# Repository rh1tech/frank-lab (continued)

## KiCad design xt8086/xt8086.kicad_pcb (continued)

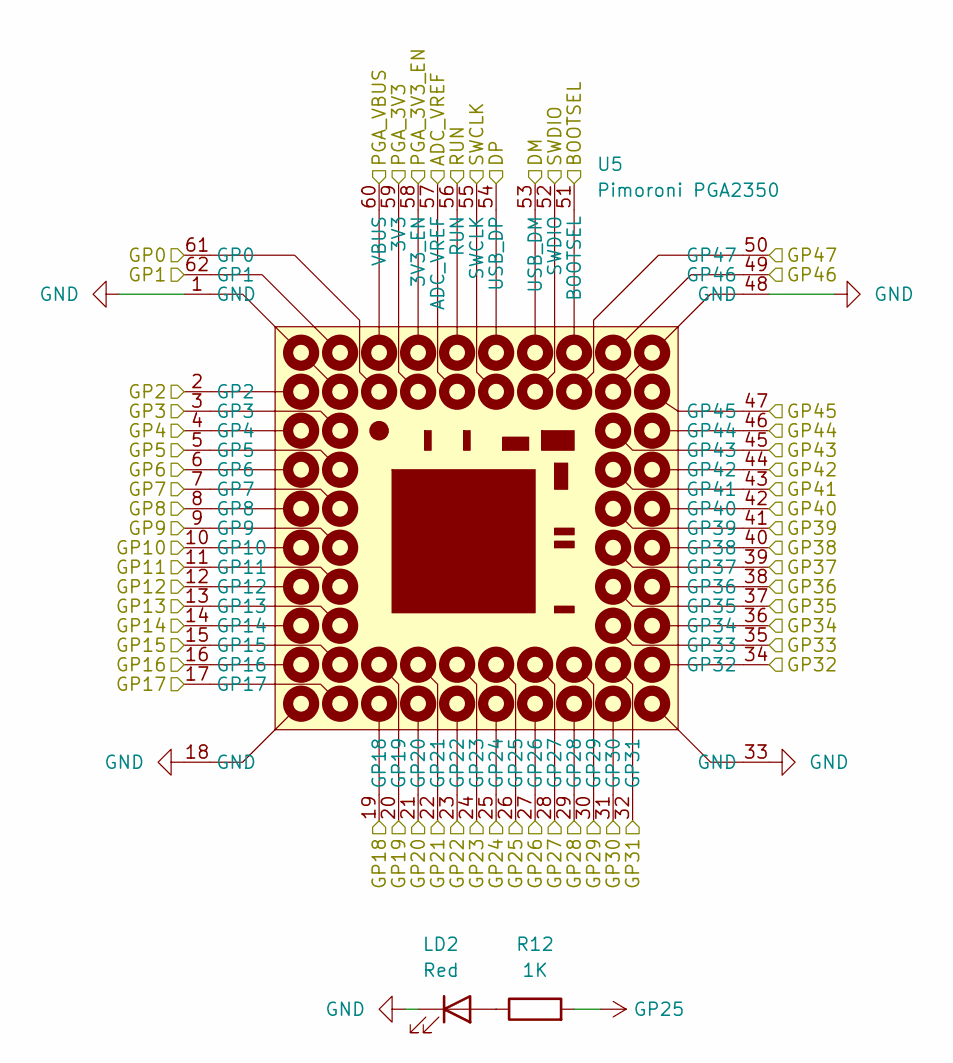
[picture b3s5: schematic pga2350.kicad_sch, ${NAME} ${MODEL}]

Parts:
LD2: Red; LED_0805_2012Metric_Pad1.15x1.40mm_HandSolder
R12: 1K; R_0805_2012Metric
U5: Pimoroni PGA2350; PGA2350

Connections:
+3V3: U5.59 (3V3); also elsewhere on the board
/A16/GP16: U5.16 (GP16); also elsewhere on the board
/A17/GP17: U5.17 (GP17); also elsewhere on the board
/A18/GP18: U5.19 (GP18); also elsewhere on the board
/A19/GP19: U5.20 (GP19); also elsewhere on the board
/AD0/GP0: U5.61 (GP0); also elsewhere on the board
/AD1/GP1: U5.62 (GP1); also elsewhere on the board
/AD2/GP2: U5.2 (GP2); also elsewhere on the board
/AD3/GP3: U5.3 (GP3); also elsewhere on the board
/AD4/GP4: U5.4 (GP4); also elsewhere on the board
/AD5/GP5: U5.5 (GP5); also elsewhere on the board
/AD6/GP6: U5.6 (GP6); also elsewhere on the board
/AD7/GP7: U5.7 (GP7); also elsewhere on the board
/AD8/GP8: U5.8 (GP8); also elsewhere on the board
/AD9/GP9: U5.9 (GP9); also elsewhere on the board
/AD10/GP10: U5.10 (GP10); also elsewhere on the board
/AD11/GP11: U5.11 (GP11); also elsewhere on the board
/AD12/GP12: U5.12 (GP12); also elsewhere on the board
/AD13/GP13: U5.13 (GP13); also elsewhere on the board
/AD14/GP14: U5.14 (GP14); also elsewhere on the board
/AD15/GP15: U5.15 (GP15); also elsewhere on the board
/ALE/GP20: U5.21 (GP20); also elsewhere on the board
/Audio/SPEAKER: U5.49 (GP46); also elsewhere on the board
/BOOTSEL: U5.51 (BOOTSEL); also elsewhere on the board
/CLK/GP29: U5.30 (GP29); also elsewhere on the board
/GP27: U5.28 (GP27); also elsewhere on the board
/INTA/GP23: U5.24 (GP23); also elsewhere on the board
/INTR/GP26: U5.27 (GP26); also elsewhere on the board
/MIO/GP24: U5.25 (GP24); also elsewhere on the board
/Micro SD/CDDAT3: U5.43 (GP41); also elsewhere on the board
/Micro SD/CLK: U5.44 (GP42); also elsewhere on the board
/Micro SD/CMD: U5.45 (GP43); also elsewhere on the board
/Micro SD/DAT0: U5.42 (GP40); also elsewhere on the board
/PGA2350/ADC_VREF: U5.57 (ADC_VREF)
/PGA2350/DM: U5.53 (USB_DM); also elsewhere on the board
/PGA2350/DP: U5.54 (USB_DP); also elsewhere on the board
/PGA2350/GP30: U5.31 (GP30); also elsewhere on the board
/PGA2350/GP31: U5.32 (GP31); also elsewhere on the board
/PGA2350/GP32: U5.34 (GP32); also elsewhere on the board
/PGA2350/GP33: U5.35 (GP33); also elsewhere on the board
/PGA2350/GP34: U5.36 (GP34); also elsewhere on the board
/PGA2350/GP35: U5.37 (GP35); also elsewhere on the board
/PGA2350/GP36: U5.38 (GP36); also elsewhere on the board
/PGA2350/GP37: U5.39 (GP37); also elsewhere on the board
/PGA2350/GP38: U5.40 (GP38)
/PGA2350/GP39: U5.41 (GP39)
/PGA2350/GP47: U5.50 (GP47)
/PGA2350/PGA_3V3_EN: U5.58 (3V3_EN)
/RD/GP21: U5.22 (GP21); also elsewhere on the board
/RESET/GP28: U5.29 (GP28); also elsewhere on the board
/RUN: U5.56 (RUN); also elsewhere on the board
/SWCLK: U5.55 (SWCLK); also elsewhere on the board
/SWDIO: U5.52 (SWDIO); also elsewhere on the board
/UART0_RX: U5.47 (GP45); also elsewhere on the board
/UART0_TX: U5.46 (GP44); also elsewhere on the board
/WR/GP22: U5.23 (GP22); also elsewhere on the board
GND: LD2.1 (K), U5.1 (GND), U5.18 (GND), U5.33 (GND), U5.48 (GND); also elsewhere on the board
GP25: R12.2, U5.26 (GP25); also elsewhere on the board
unnamed: LD2.2 (A), R12.1
VBUS: U5.60 (VBUS); also elsewhere on the board

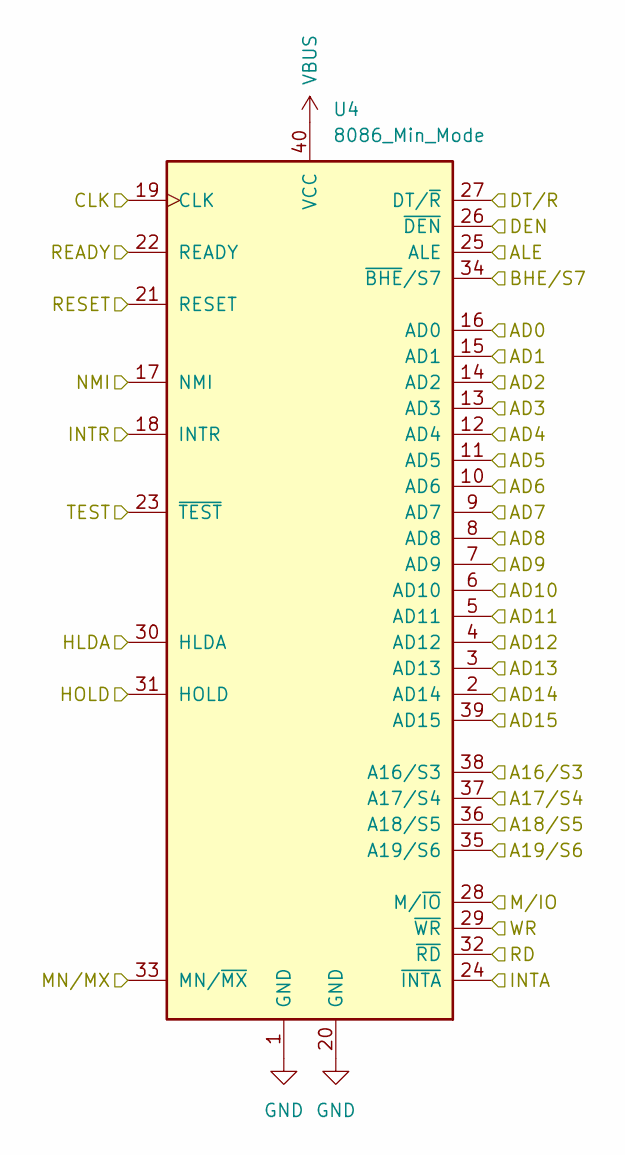
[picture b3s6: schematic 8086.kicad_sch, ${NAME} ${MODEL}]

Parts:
U4: 8086_Min_Mode; DIP-40_W15.24mm

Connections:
/A16/GP16: U4.38 (A16/S3); also elsewhere on the board
/A17/GP17: U4.37 (A17/S4); also elsewhere on the board
/A18/GP18: U4.36 (A18/S5); also elsewhere on the board
/A19/GP19: U4.35 (A19/S6); also elsewhere on the board
/AD0/GP0: U4.16 (AD0); also elsewhere on the board
/AD1/GP1: U4.15 (AD1); also elsewhere on the board
/AD2/GP2: U4.14 (AD2); also elsewhere on the board
/AD3/GP3: U4.13 (AD3); also elsewhere on the board
/AD4/GP4: U4.12 (AD4); also elsewhere on the board
/AD5/GP5: U4.11 (AD5); also elsewhere on the board
/AD6/GP6: U4.10 (AD6); also elsewhere on the board
/AD7/GP7: U4.9 (AD7); also elsewhere on the board
/AD8/GP8: U4.8 (AD8); also elsewhere on the board
/AD9/GP9: U4.7 (AD9); also elsewhere on the board
/AD10/GP10: U4.6 (AD10); also elsewhere on the board
/AD11/GP11: U4.5 (AD11); also elsewhere on the board
/AD12/GP12: U4.4 (AD12); also elsewhere on the board
/AD13/GP13: U4.3 (AD13); also elsewhere on the board
/AD14/GP14: U4.2 (AD14); also elsewhere on the board
/AD15/GP15: U4.39 (AD15); also elsewhere on the board
/ALE/GP20: U4.25 (ALE); also elsewhere on the board
/CLK/GP29: U4.19 (CLK); also elsewhere on the board
/DEN: U4.26 (~DEN); also elsewhere on the board
/DT/R: U4.27 (DT/~R); also elsewhere on the board
/HLDA: U4.30 (HLDA); also elsewhere on the board
/INTA/GP23: U4.24 (~INTA); also elsewhere on the board
/INTR/GP26: U4.18 (INTR); also elsewhere on the board
/MIO/GP24: U4.28 (M/~IO); also elsewhere on the board
/MN/MX: U4.33 (MN/~MX); also elsewhere on the board
/RD/GP21: U4.32 (~RD); also elsewhere on the board
/READY: U4.22 (READY); also elsewhere on the board
/RESET/GP28: U4.21 (RESET); also elsewhere on the board
/TEST: U4.23 (~TEST); also elsewhere on the board
/WR/GP22: U4.29 (~WR); also elsewhere on the board
GND: U4.1 (GND), U4.17 (NMI), U4.20 (GND), U4.31 (HOLD); also elsewhere on the board
GP25: U4.34 (~BHE/S7); also elsewhere on the board
VBUS: U4.40 (VCC); also elsewhere on the board

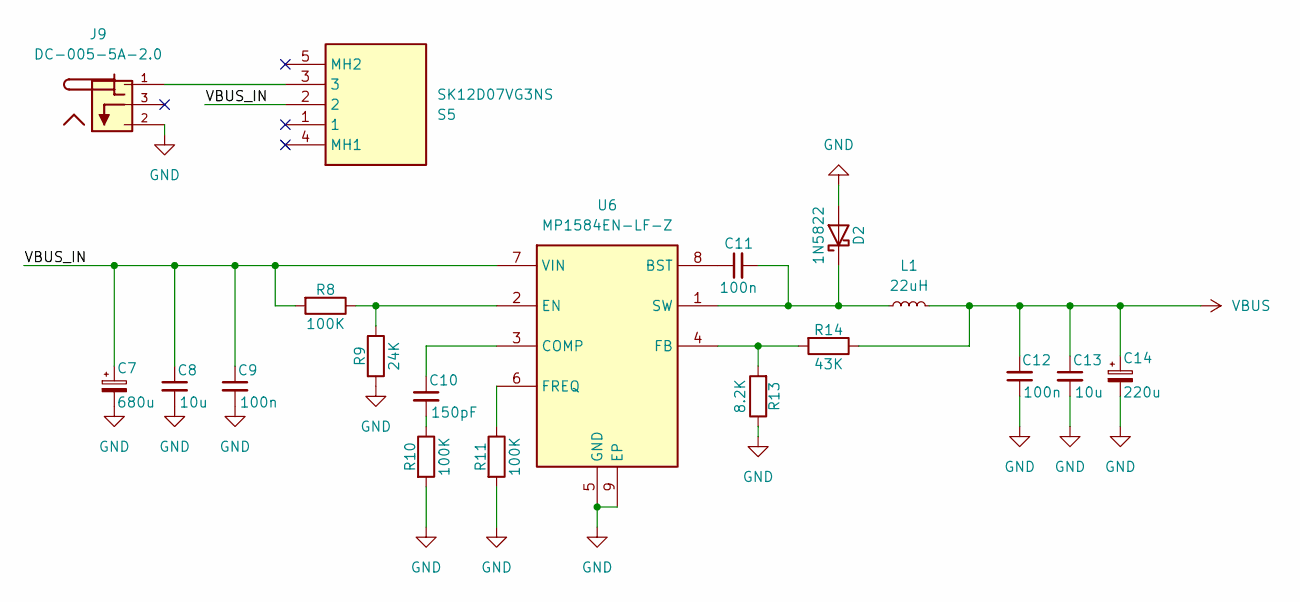
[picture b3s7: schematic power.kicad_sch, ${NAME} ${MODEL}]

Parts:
C7: 680u; C_Radial_D8.0mm_P3.50mm
C8, C13: 10u; C_0805_2012Metric
C9, C11, C12: 100n; C_0805_2012Metric
C10: 150pF; R_0805_2012Metric
C14: 220u; C_Radial_D6.3mm_P2.50mm
D2: 1N5822; D_SMA
J9: DC-005-5A-2.0; BarrelJack_DC-005; PARTREV A0
L1: 22uH; L_Radial_D9.5mm_P5.00mm_Fastron_07HVP
R8, R10, R11: 100K; R_0805_2012Metric
R9: 24K; R_0805_2012Metric
R13: 8.2K; R_0805_2012Metric
R14: 43K; R_0805_2012Metric
S5: SK12D07VG3NS; Switch_Slide_SK12D07VG3NS; Mouser Part Number 611-SK12D07VG3NS
U6: MP1584EN-LF-Z; SOIC-9_P1.27mm; Mouser Part Number 946-MP1584ENLFZ

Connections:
/Power/VBUS_IN: C7.1, C8.1, C9.1, R8.2, S5.2, U6.7 (VIN)
GND: C7.2, C8.2, C9.2, C12.1, C13.2, C14.2, D2.2 (A), J9.2, R9.2, R10.2, R11.2, R13.1, U6.5 (GND), U6.9 (EP); also elsewhere on the board
unnamed: C10.2, R10.1
unnamed: C11.2, D2.1 (K), L1.1, U6.1 (SW)
unnamed: J9.1, S5.3
unnamed: C11.1, U6.8 (BST)
unnamed: C10.1, U6.3 (COMP)
unnamed: R8.1, R9.1, U6.2 (EN)
unnamed: R13.2, R14.2, U6.4 (FB)
unnamed: R11.1, U6.6 (FREQ)
VBUS: C12.2, C13.1, C14.1, L1.2, R14.1; also elsewhere on the board

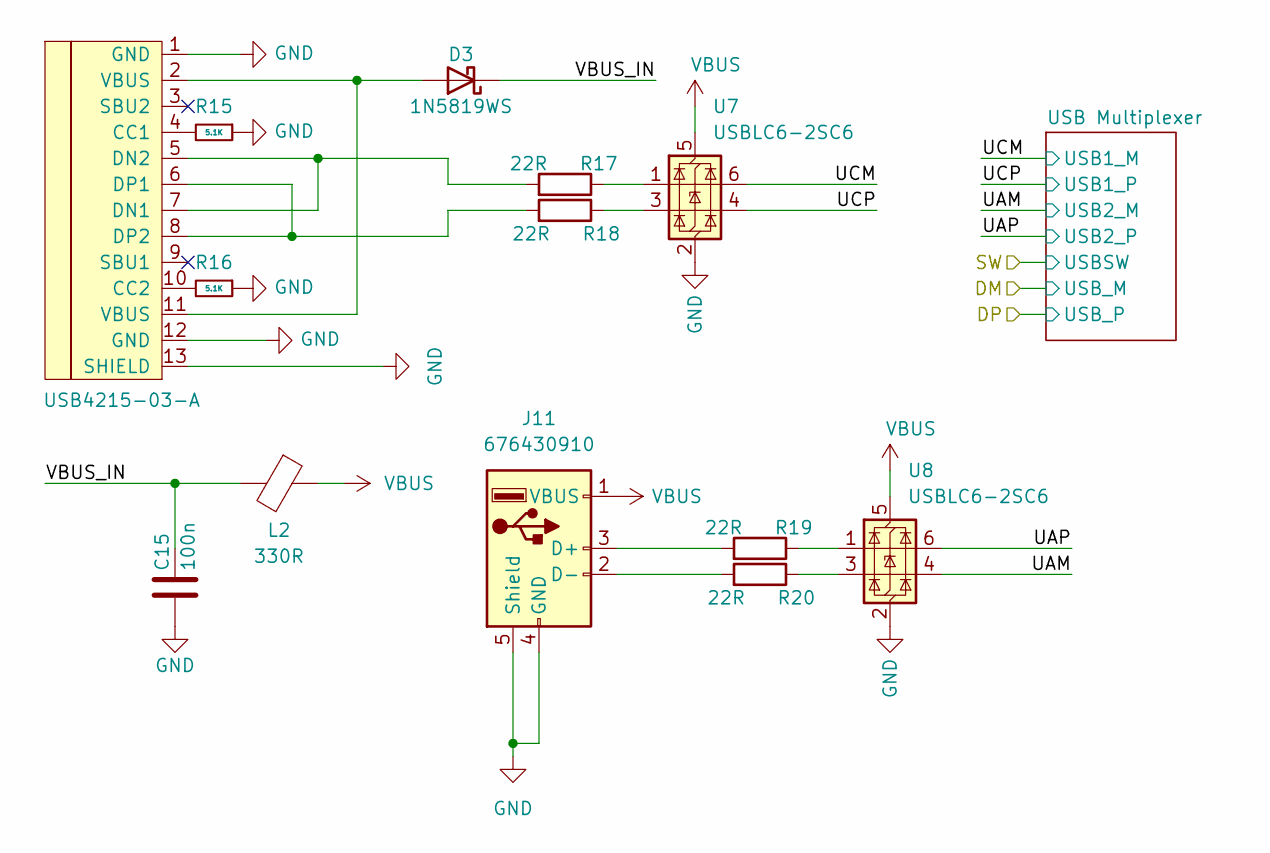
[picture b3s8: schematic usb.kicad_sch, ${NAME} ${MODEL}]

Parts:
C15: 100n; C_0805_2012Metric
D3: 1N5819WS; D_SOD-323
J10: USB4215-03-A; USB_C_Receptacle; LCSC C165948
J11: 676430910; USB_A_Single
L2: 330R; R_0805_2012Metric
R15, R16: 5.1K; R_0805_2012Metric
R17, R18, R19, R20: 22R; R_0805_2012Metric
U7, U8: USBLC6-2SC6; SOT-23-6

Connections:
/USB/UAM: U8.4 (I/O2); also elsewhere on the board
/USB/UAP: U8.6 (I/O1); also elsewhere on the board
/USB/UCM: U7.6 (I/O1); also elsewhere on the board
/USB/UCP: U7.4 (I/O2); also elsewhere on the board
/USB/VBUS_IN: C15.1, D3.1 (K), L2.2
GND: C15.2, J10.1 (GND), J10.12 (GND), J10.13 (SHIELD), J11.4 (GND), J11.5 (Shield), R15.1, R16.1, U7.2 (GND), U8.2 (GND); also elsewhere on the board
unnamed: D3.2 (A), J10.2 (VBUS), J10.11 (VBUS)
unnamed: J10.4 (CC1), R15.2
unnamed: J10.10 (CC2), R16.2
unnamed: J10.5 (DN2), J10.7 (DN1), R17.2
unnamed: J10.6 (DP1), J10.8 (DP2), R18.2
unnamed: J11.3 (D+), R19.2
unnamed: J11.2 (D-), R20.2
unnamed: R17.1, U7.1 (I/O1)
unnamed: R18.1, U7.3 (I/O2)
unnamed: R19.1, U8.1 (I/O1)
unnamed: R20.1, U8.3 (I/O2)
VBUS: J11.1 (VBUS), L2.1, U7.5 (VBUS), U8.5 (VBUS); also elsewhere on the board

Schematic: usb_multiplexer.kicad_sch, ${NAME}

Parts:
C5: 100n; C_0805_2012Metric
R4: 10K; R_0805_2012Metric
U3: 74HC4052D; 74HC4052N; Mouser Part Number 771-74HC4052D-T

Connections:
/PGA2350/DM: U3.3 (2Z); also elsewhere on the board
/PGA2350/DP: U3.13 (1Z); also elsewhere on the board
/USB/SW: R4.2, U3.10 (S0); also elsewhere on the board
/USB/UAM: U3.5 (2Y1); also elsewhere on the board
/USB/UAP: U3.14 (1Y1); also elsewhere on the board
/USB/UCM: U3.1 (2Y0); also elsewhere on the board
/USB/UCP: U3.12 (1Y0); also elsewhere on the board
GND: C5.1, R4.1, U3.2 (2Y2), U3.4 (2Y3), U3.6 (~E), U3.7 (VEE), U3.8 (GND), U3.9 (S1), U3.11 (1Y3), U3.15 (1Y2); also elsewhere on the board
VBUS: C5.2, U3.16 (VCC); also elsewhere on the board

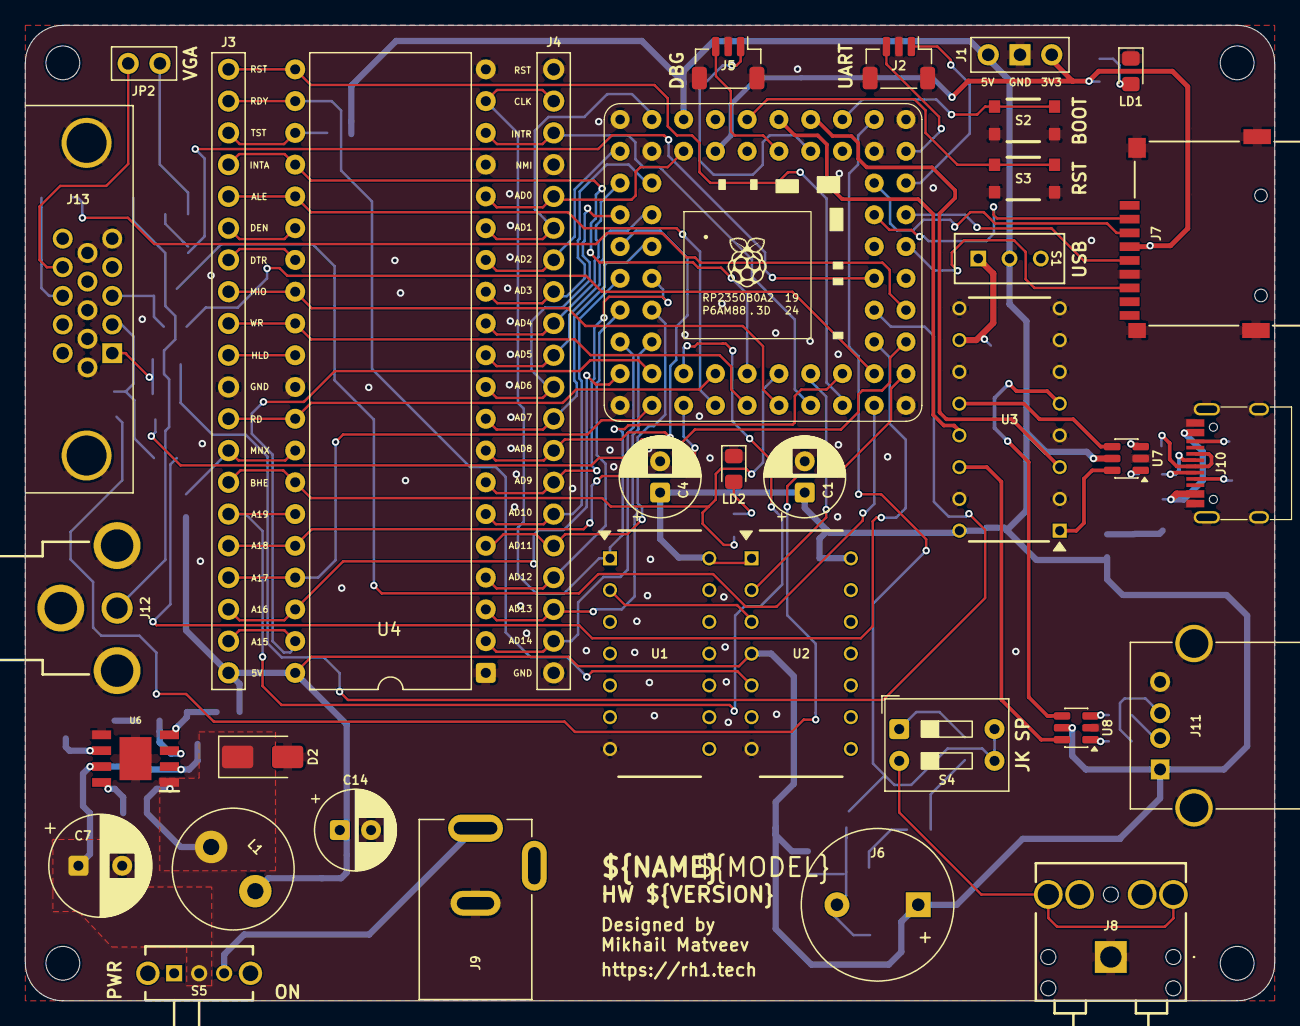
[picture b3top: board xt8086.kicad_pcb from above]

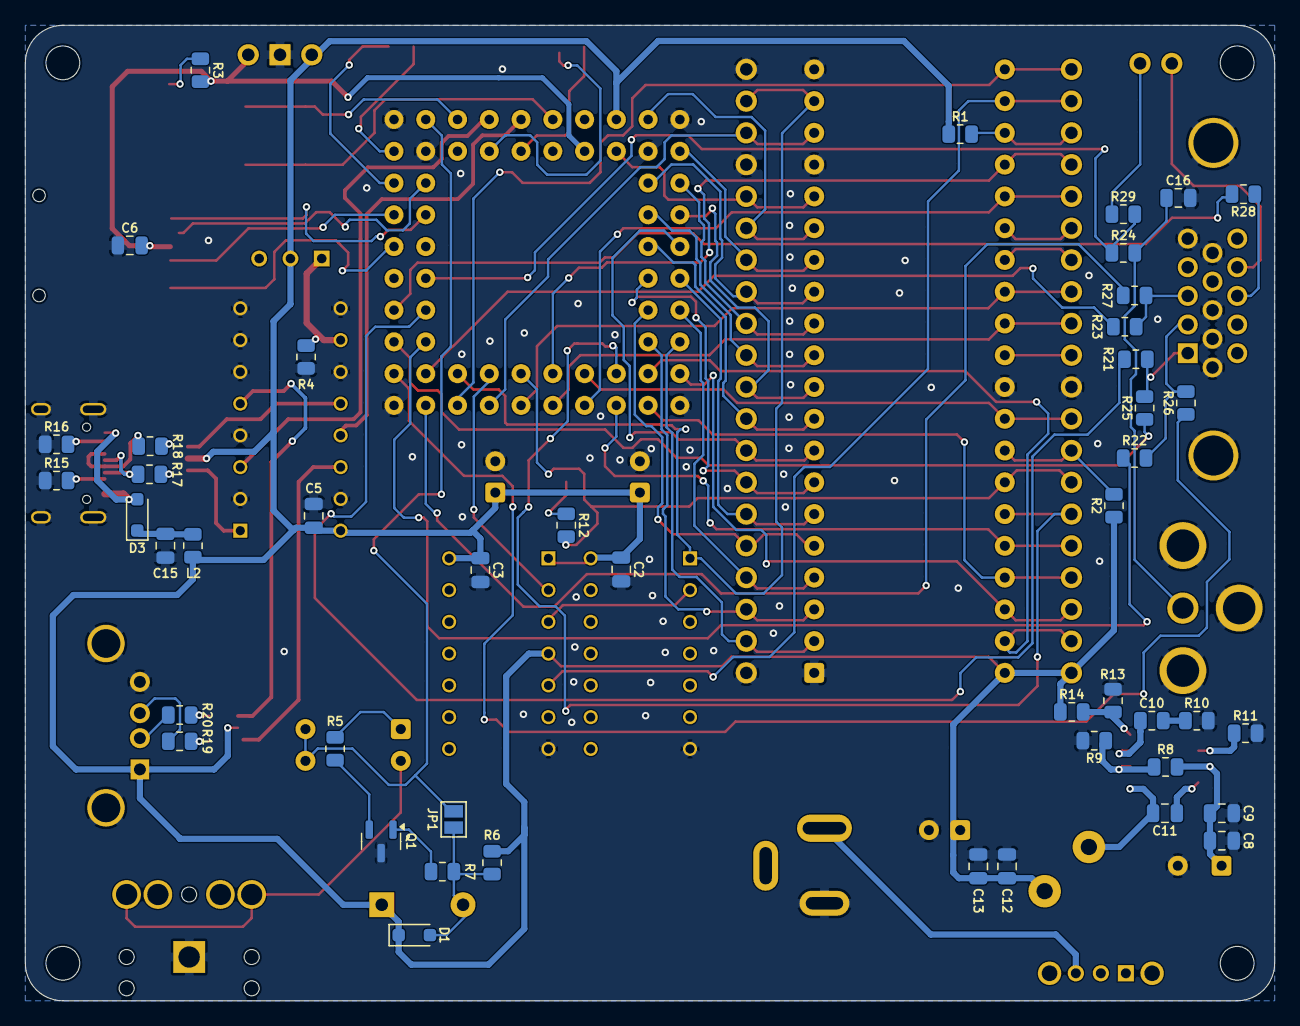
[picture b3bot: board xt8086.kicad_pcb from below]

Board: 2 copper layers, 99.9 x 78.0 mm, 85 parts (46 on the bottom side), 101 nets.
